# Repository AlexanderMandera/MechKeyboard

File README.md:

# Custom Keyboard PCB (WIP)

### by Alexander Mandera

Please refer to the KiCad files if you want up-to-date images.

## ToDo

- Check if USB traces are alright
- Add holes for 3d printed case

# Layout

[Permalink to keyboard-layout-editor.com](http://www.keyboard-layout-editor.com/##@@=Esc&_x:1%3B&=F1&=F2&=F3&=F4&_x:0.5%3B&=F5&=F6&=F7&=F8&_x:0.5%3B&=F9&=F10&=F11&=F12&_x:0.25%3B&=PrtSc&=Scroll%20Lock&=Pause%0ABreak%3B&@_y:0.5%3B&=%C2%B0%0A%5E&=!%0A1&=%22%0A2&=%C2%A7%0A3&=$%0A4&=%25%0A5&=%2F&%0A6&=%2F%2F%0A7&=(%0A8&=)%0A9&=%2F=%0A0&=%3F%0A%C3%9F&=%60%0A%C2%B4&_w:2%3B&=Backspace&_x:0.25%3B&=Insert&=Home&=PgUp&_x:0.25%3B&=Num%20Lock&=%2F%2F&=*&=-%3B&@_w:1.5%3B&=Tab&=Q&=W&=E&=R&=T&=Z&=U&=I&=O&=P&=%C3%9C&=*%0A+&_x:0.25&w:1.25&h:2&w2:1.5&h2:1&x2:-0.25%3B&=Enter&_x:0.25%3B&=Delete&=End&=PgDn&_x:0.25%3B&=7%0AHome&=8%0A%E2%86%91&=9%0APgUp&_h:2%3B&=+%3B&@_w:1.75%3B&=Caps%20Lock&=A&=S&=D&=F&=G&=H&=J&=K&=L&=%C3%96&=%C3%84&='%0A%23&_x:4.75%3B&=4%0A%E2%86%90&=5&=6%0A%E2%86%92%3B&@_w:1.25%3B&=Shift&=%3E%0A%3C&=Y&=X&=C&=V&=B&=N&=M&=%2F%3B%0A,&=%2F:%0A.&=%2F_%0A-&_w:2.75%3B&=Shift&_x:1.25%3B&=%E2%86%91&_x:1.25%3B&=1%0AEnd&=2%0A%E2%86%93&=3%0APgDn&_h:2%3B&=Enter%3B&@_w:1.25%3B&=Ctrl&_w:1.25%3B&=Win&_w:1.25%3B&=Alt&_a:7&w:6.25%3B&=&_a:4&w:1.25%3B&=AltGr&_w:1.25%3B&=Win&_w:1.25%3B&=Menu&_w:1.25%3B&=Ctrl&_x:0.25%3B&=%E2%86%90&=%E2%86%93&=%E2%86%92&_x:0.25&w:2%3B&=0%0AIns&=.%0ADel)

# PCB

#### Schematic

#### Matrix

#### PCB (Routing)

### PCB (Render)

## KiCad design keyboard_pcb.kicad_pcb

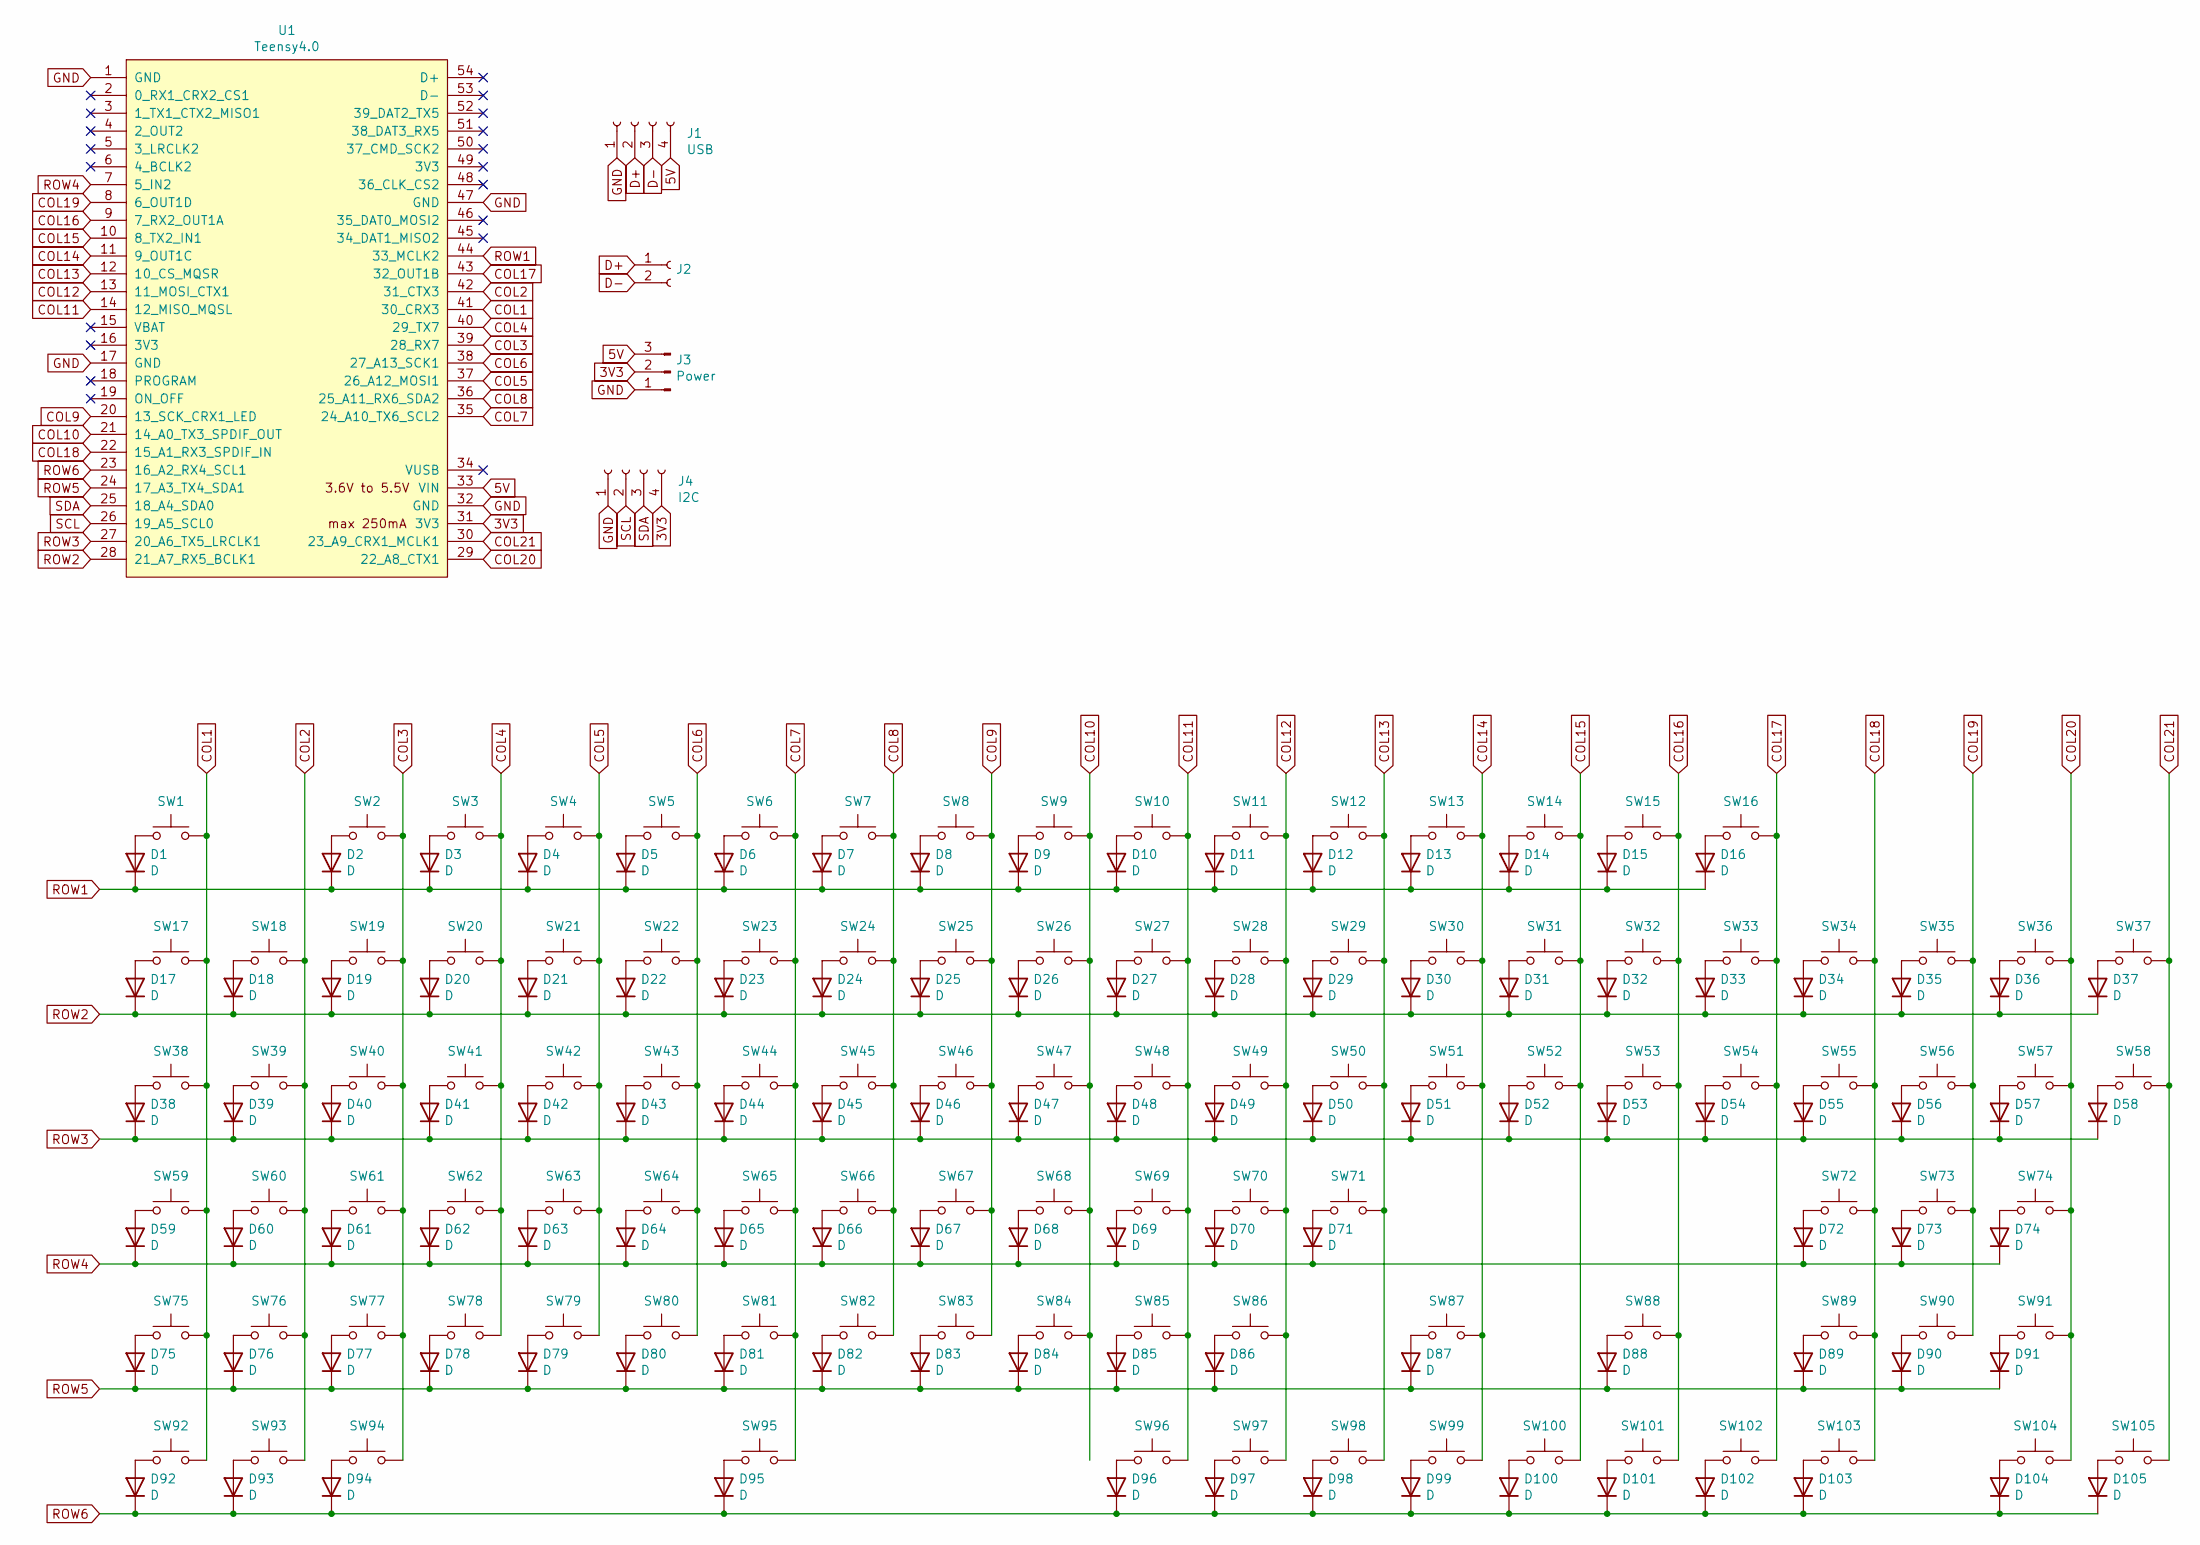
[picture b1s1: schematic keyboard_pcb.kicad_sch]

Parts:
D1, D2, D3, D4, D5, D6, D7, D8, D9, D10, D11, D12, D13, D14, D15, D16, D17, D18, D19, D20, D21, D22, D23, D24, D25, D26, D27, D28, D29, D30, D31, D32, D33, D34, D35, D36, D37, D38, D39, D40, D41, D42, D43, D44, D45, D46, D47, D48, D49, D50, D51, D52, D53, D54, D55, D56, D57, D58, D59, D60, D61, D62, D63, D64, D65, D66, D67, D68, D69, D70, D71, D72, D73, D74, D75, D76, D77, D78, D79, D80, D81, D82, D83, D84, D85, D86, D87, D88, D89, D90, D91, D92, D93, D94, D95, D96, D97, D98, D99, D100, D101, D102, D103, D104, D105: D; D_DO-35_SOD27_P7.62mm_Horizontal
J1: USB; PinHeader_1x04_P2.54mm_Vertical
J2: PinHeader_1x02_P2.54mm_Vertical
J3: Power; PinHeader_1x03_P2.54mm_Vertical
J4: I2C; PinHeader_1x04_P2.54mm_Vertical
SW1, SW2, SW3, SW4, SW5, SW6, SW7, SW8, SW9, SW10, SW11, SW12, SW13, SW14, SW15, SW16, SW17, SW18, SW19, SW20, SW21, SW22, SW23, SW24, SW25, SW26, SW27, SW28, SW29, SW31, SW32, SW33, SW34, SW35, SW36, SW37, SW39, SW40, SW41, SW42, SW43, SW44, SW45, SW46, SW47, SW48, SW49, SW50, SW52, SW53, SW54, SW55, SW56, SW57, SW60, SW61, SW62, SW63, SW64, SW65, SW66, SW67, SW68, SW69, SW70, SW71, SW72, SW73, SW74, SW76, SW77, SW78, SW79, SW80, SW81, SW82, SW83, SW84, SW85, SW86, SW88, SW89, SW90, SW91, SW100, SW101, SW102, SW104: SW_Push; SW_Cherry_MX_1.00u_PCB
SW30, SW103: SW_Push; SW_Cherry_MX_2.00u_PCB
SW38: SW_Push; SW_Cherry_MX_1.50u_PCB
SW51: SW_Push; SW_Cherry_MX_ISOEnter_PCB
SW58, SW105: SW_Push; SW_Cherry_MX_2.00u_Vertical_PCB
SW59: SW_Push; SW_Cherry_MX_1.75u_PCB
SW75, SW92, SW93, SW94, SW96, SW97, SW98, SW99: SW_Push; SW_Cherry_MX_1.25u_PCB
SW87: SW_Push; SW_Cherry_MX_2.75u_PCB
SW95: SW_Push; SW_Cherry_MX_6.25u_PCB
U1: Teensy4.0; Teensy40_Remove_Last_Col

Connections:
3V3: J3.2, J4.4, U1.31 (3V3)
5V: J1.4, J3.3, U1.33 (VIN)
COL1: SW1.2, SW17.2, SW38.2, SW59.2, SW75.2, SW92.2, U1.41 (30_CRX3)
COL2: SW18.2, SW39.2, SW60.2, SW76.2, SW93.2, U1.42 (31_CTX3)
COL3: SW2.2, SW19.2, SW40.2, SW61.2, SW77.2, SW94.2, U1.39 (28_RX7)
COL4: SW3.2, SW20.2, SW41.2, SW62.2, SW78.2, U1.40 (29_TX7)
COL5: SW4.2, SW21.2, SW42.2, SW63.2, SW79.2, U1.37 (26_A12_MOSI1)
COL6: SW5.2, SW22.2, SW43.2, SW64.2, SW80.2, U1.38 (27_A13_SCK1)
COL7: SW6.2, SW23.2, SW44.2, SW65.2, SW81.2, SW95.2, U1.35 (24_A10_TX6_SCL2)
COL8: SW7.2, SW24.2, SW45.2, SW66.2, SW82.2, U1.36 (25_A11_RX6_SDA2)
COL9: SW8.2, SW25.2, SW46.2, SW67.2, SW83.2, U1.20 (13_SCK_CRX1_LED)
COL10: SW9.2, SW26.2, SW47.2, SW68.2, SW84.2, U1.21 (14_A0_TX3_SPDIF_OUT)
COL11: SW10.2, SW27.2, SW48.2, SW69.2, SW85.2, SW96.2, U1.14 (12_MISO_MQSL)
COL12: SW11.2, SW28.2, SW49.2, SW70.2, SW86.2, SW97.2, U1.13 (11_MOSI_CTX1)
COL13: SW12.2, SW29.2, SW50.2, SW71.2, SW98.2, U1.12 (10_CS_MQSR)
COL14: SW13.2, SW30.2, SW51.2, SW87.2, SW99.2, U1.11 (9_OUT1C)
COL15: SW14.2, SW31.2, SW52.2, SW100.2, U1.10 (8_TX2_IN1)
COL16: SW15.2, SW32.2, SW53.2, SW88.2, SW101.2, U1.9 (7_RX2_OUT1A)
COL17: SW16.2, SW33.2, SW54.2, SW102.2, U1.43 (32_OUT1B)
COL18: SW34.2, SW55.2, SW72.2, SW89.2, SW103.2, U1.22 (15_A1_RX3_SPDIF_IN)
COL19: SW35.2, SW56.2, SW73.2, SW90.2, U1.8 (6_OUT1D)
COL20: SW36.2, SW57.2, SW74.2, SW91.2, SW104.2, U1.29 (22_A8_CTX1)
COL21: SW37.2, SW58.2, SW105.2, U1.30 (23_A9_CRX1_MCLK1)
D+: J1.2, J2.1
D-: J1.3, J2.2
GND: J1.1, J3.1, J4.1, U1.1 (GND), U1.17 (GND), U1.32 (GND), U1.47 (GND)
unnamed: D1.2 (A), SW1.1
unnamed: D2.2 (A), SW2.1
unnamed: D3.2 (A), SW3.1
unnamed: D4.2 (A), SW4.1
unnamed: D5.2 (A), SW5.1
unnamed: D6.2 (A), SW6.1
unnamed: D7.2 (A), SW7.1
unnamed: D8.2 (A), SW8.1
unnamed: D9.2 (A), SW9.1
unnamed: D10.2 (A), SW10.1
unnamed: D11.2 (A), SW11.1
unnamed: D12.2 (A), SW12.1
unnamed: D13.2 (A), SW13.1
unnamed: D14.2 (A), SW14.1
unnamed: D15.2 (A), SW15.1
unnamed: D16.2 (A), SW16.1
unnamed: D17.2 (A), SW17.1
unnamed: D18.2 (A), SW18.1
unnamed: D19.2 (A), SW19.1
unnamed: D20.2 (A), SW20.1
unnamed: D21.2 (A), SW21.1
unnamed: D22.2 (A), SW22.1
unnamed: D23.2 (A), SW23.1
unnamed: D24.2 (A), SW24.1
unnamed: D25.2 (A), SW25.1
unnamed: D26.2 (A), SW26.1
unnamed: D27.2 (A), SW27.1
unnamed: D28.2 (A), SW28.1
unnamed: D29.2 (A), SW29.1
unnamed: D30.2 (A), SW30.1
unnamed: D31.2 (A), SW31.1
unnamed: D32.2 (A), SW32.1
unnamed: D33.2 (A), SW33.1
unnamed: D34.2 (A), SW34.1
unnamed: D35.2 (A), SW35.1
unnamed: D36.2 (A), SW36.1
unnamed: D37.2 (A), SW37.1
unnamed: D38.2 (A), SW38.1
unnamed: D39.2 (A), SW39.1
unnamed: D40.2 (A), SW40.1
unnamed: D41.2 (A), SW41.1
unnamed: D42.2 (A), SW42.1
unnamed: D43.2 (A), SW43.1
unnamed: D44.2 (A), SW44.1
unnamed: D45.2 (A), SW45.1
unnamed: D46.2 (A), SW46.1
unnamed: D47.2 (A), SW47.1
unnamed: D48.2 (A), SW48.1
unnamed: D49.2 (A), SW49.1
unnamed: D50.2 (A), SW50.1
unnamed: D51.2 (A), SW51.1
unnamed: D52.2 (A), SW52.1
unnamed: D53.2 (A), SW53.1
unnamed: D54.2 (A), SW54.1
unnamed: D55.2 (A), SW55.1
unnamed: D56.2 (A), SW56.1
unnamed: D57.2 (A), SW57.1
unnamed: D58.2 (A), SW58.1
unnamed: D59.2 (A), SW59.1
unnamed: D60.2 (A), SW60.1
unnamed: D61.2 (A), SW61.1
unnamed: D62.2 (A), SW62.1
unnamed: D63.2 (A), SW63.1
unnamed: D64.2 (A), SW64.1
unnamed: D65.2 (A), SW65.1
unnamed: D66.2 (A), SW66.1
unnamed: D67.2 (A), SW67.1
unnamed: D68.2 (A), SW68.1
unnamed: D69.2 (A), SW69.1
unnamed: D70.2 (A), SW70.1
unnamed: D71.2 (A), SW71.1
unnamed: D72.2 (A), SW72.1
unnamed: D73.2 (A), SW73.1
unnamed: D74.2 (A), SW74.1
unnamed: D75.2 (A), SW75.1
unnamed: D76.2 (A), SW76.1
unnamed: D77.2 (A), SW77.1
unnamed: D78.2 (A), SW78.1
unnamed: D79.2 (A), SW79.1
unnamed: D80.2 (A), SW80.1
unnamed: D81.2 (A), SW81.1
unnamed: D82.2 (A), SW82.1
unnamed: D83.2 (A), SW83.1
unnamed: D84.2 (A), SW84.1
unnamed: D85.2 (A), SW85.1
unnamed: D86.2 (A), SW86.1
unnamed: D87.2 (A), SW87.1
unnamed: D88.2 (A), SW88.1
unnamed: D89.2 (A), SW89.1
unnamed: D90.2 (A), SW90.1
unnamed: D91.2 (A), SW91.1
unnamed: D92.2 (A), SW92.1
unnamed: D93.2 (A), SW93.1
unnamed: D94.2 (A), SW94.1
unnamed: D95.2 (A), SW95.1
unnamed: D96.2 (A), SW96.1
unnamed: D97.2 (A), SW97.1
unnamed: D98.2 (A), SW98.1
unnamed: D99.2 (A), SW99.1
unnamed: D100.2 (A), SW100.1
unnamed: D101.2 (A), SW101.1
unnamed: D102.2 (A), SW102.1
unnamed: D103.2 (A), SW103.1
unnamed: D104.2 (A), SW104.1
unnamed: D105.2 (A), SW105.1
ROW1: D1.1 (K), D2.1 (K), D3.1 (K), D4.1 (K), D5.1 (K), D6.1 (K), D7.1 (K), D8.1 (K), D9.1 (K), D10.1 (K), D11.1 (K), D12.1 (K), D13.1 (K), D14.1 (K), D15.1 (K), D16.1 (K), U1.44 (33_MCLK2)
ROW2: D17.1 (K), D18.1 (K), D19.1 (K), D20.1 (K), D21.1 (K), D22.1 (K), D23.1 (K), D24.1 (K), D25.1 (K), D26.1 (K), D27.1 (K), D28.1 (K), D29.1 (K), D30.1 (K), D31.1 (K), D32.1 (K), D33.1 (K), D34.1 (K), D35.1 (K), D36.1 (K), D37.1 (K), U1.28 (21_A7_RX5_BCLK1)
ROW3: D38.1 (K), D39.1 (K), D40.1 (K), D41.1 (K), D42.1 (K), D43.1 (K), D44.1 (K), D45.1 (K), D46.1 (K), D47.1 (K), D48.1 (K), D49.1 (K), D50.1 (K), D51.1 (K), D52.1 (K), D53.1 (K), D54.1 (K), D55.1 (K), D56.1 (K), D57.1 (K), D58.1 (K), U1.27 (20_A6_TX5_LRCLK1)
ROW4: D59.1 (K), D60.1 (K), D61.1 (K), D62.1 (K), D63.1 (K), D64.1 (K), D65.1 (K), D66.1 (K), D67.1 (K), D68.1 (K), D69.1 (K), D70.1 (K), D71.1 (K), D72.1 (K), D73.1 (K), D74.1 (K), U1.7 (5_IN2)
ROW5: D75.1 (K), D76.1 (K), D77.1 (K), D78.1 (K), D79.1 (K), D80.1 (K), D81.1 (K), D82.1 (K), D83.1 (K), D84.1 (K), D85.1 (K), D86.1 (K), D87.1 (K), D88.1 (K), D89.1 (K), D90.1 (K), D91.1 (K), U1.24 (17_A3_TX4_SDA1)
ROW6: D92.1 (K), D93.1 (K), D94.1 (K), D95.1 (K), D96.1 (K), D97.1 (K), D98.1 (K), D99.1 (K), D100.1 (K), D101.1 (K), D102.1 (K), D103.1 (K), D104.1 (K), D105.1 (K), U1.23 (16_A2_RX4_SCL1)
SCL: J4.2, U1.26 (19_A5_SCL0)
SDA: J4.3, U1.25 (18_A4_SDA0)

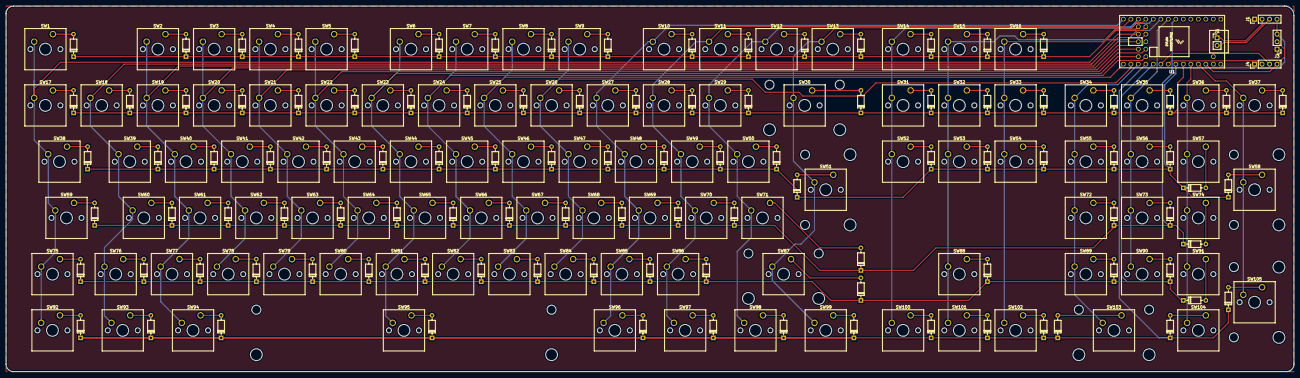
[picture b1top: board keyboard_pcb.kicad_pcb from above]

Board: 2 copper layers, 436.2 x 123.8 mm, 215 parts (0 on the bottom side), 139 nets.

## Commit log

2022-01-16 Add I2C port for OLED display
2022-01-16 Fix README
2022-01-16 Fixed missing connections and schematic changes
2022-01-16 Add 3V3 connection
2022-01-16 Split some traces
2022-01-16 Added 2 more ground connections
2022-01-16 Add background color to Teensy 4.0
2022-01-16 Put schematic onto one page
2022-01-16 Migrated to KiCad 6
2022-01-16 Moved some traces away from holes
2022-01-18 Adjusted USB data line, added holes, some decoration
2022-01-18 Add text and QMK badge
2022-01-18 Fix hole clearance error
2022-01-19 Finishing checks and add "Not in schematic" flags
2022-01-19 Add gerbers
